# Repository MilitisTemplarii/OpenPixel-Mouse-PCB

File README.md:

# OpenPixel
# Mouse-PCB-STM32-PAW3395
BOM file soon :D

This is a mouse pcb based on stm32f215, usb3300 and paw3395

NO CODE, FIRMWARE, SOFTWARE, ETC, just a pcb design for hobby.

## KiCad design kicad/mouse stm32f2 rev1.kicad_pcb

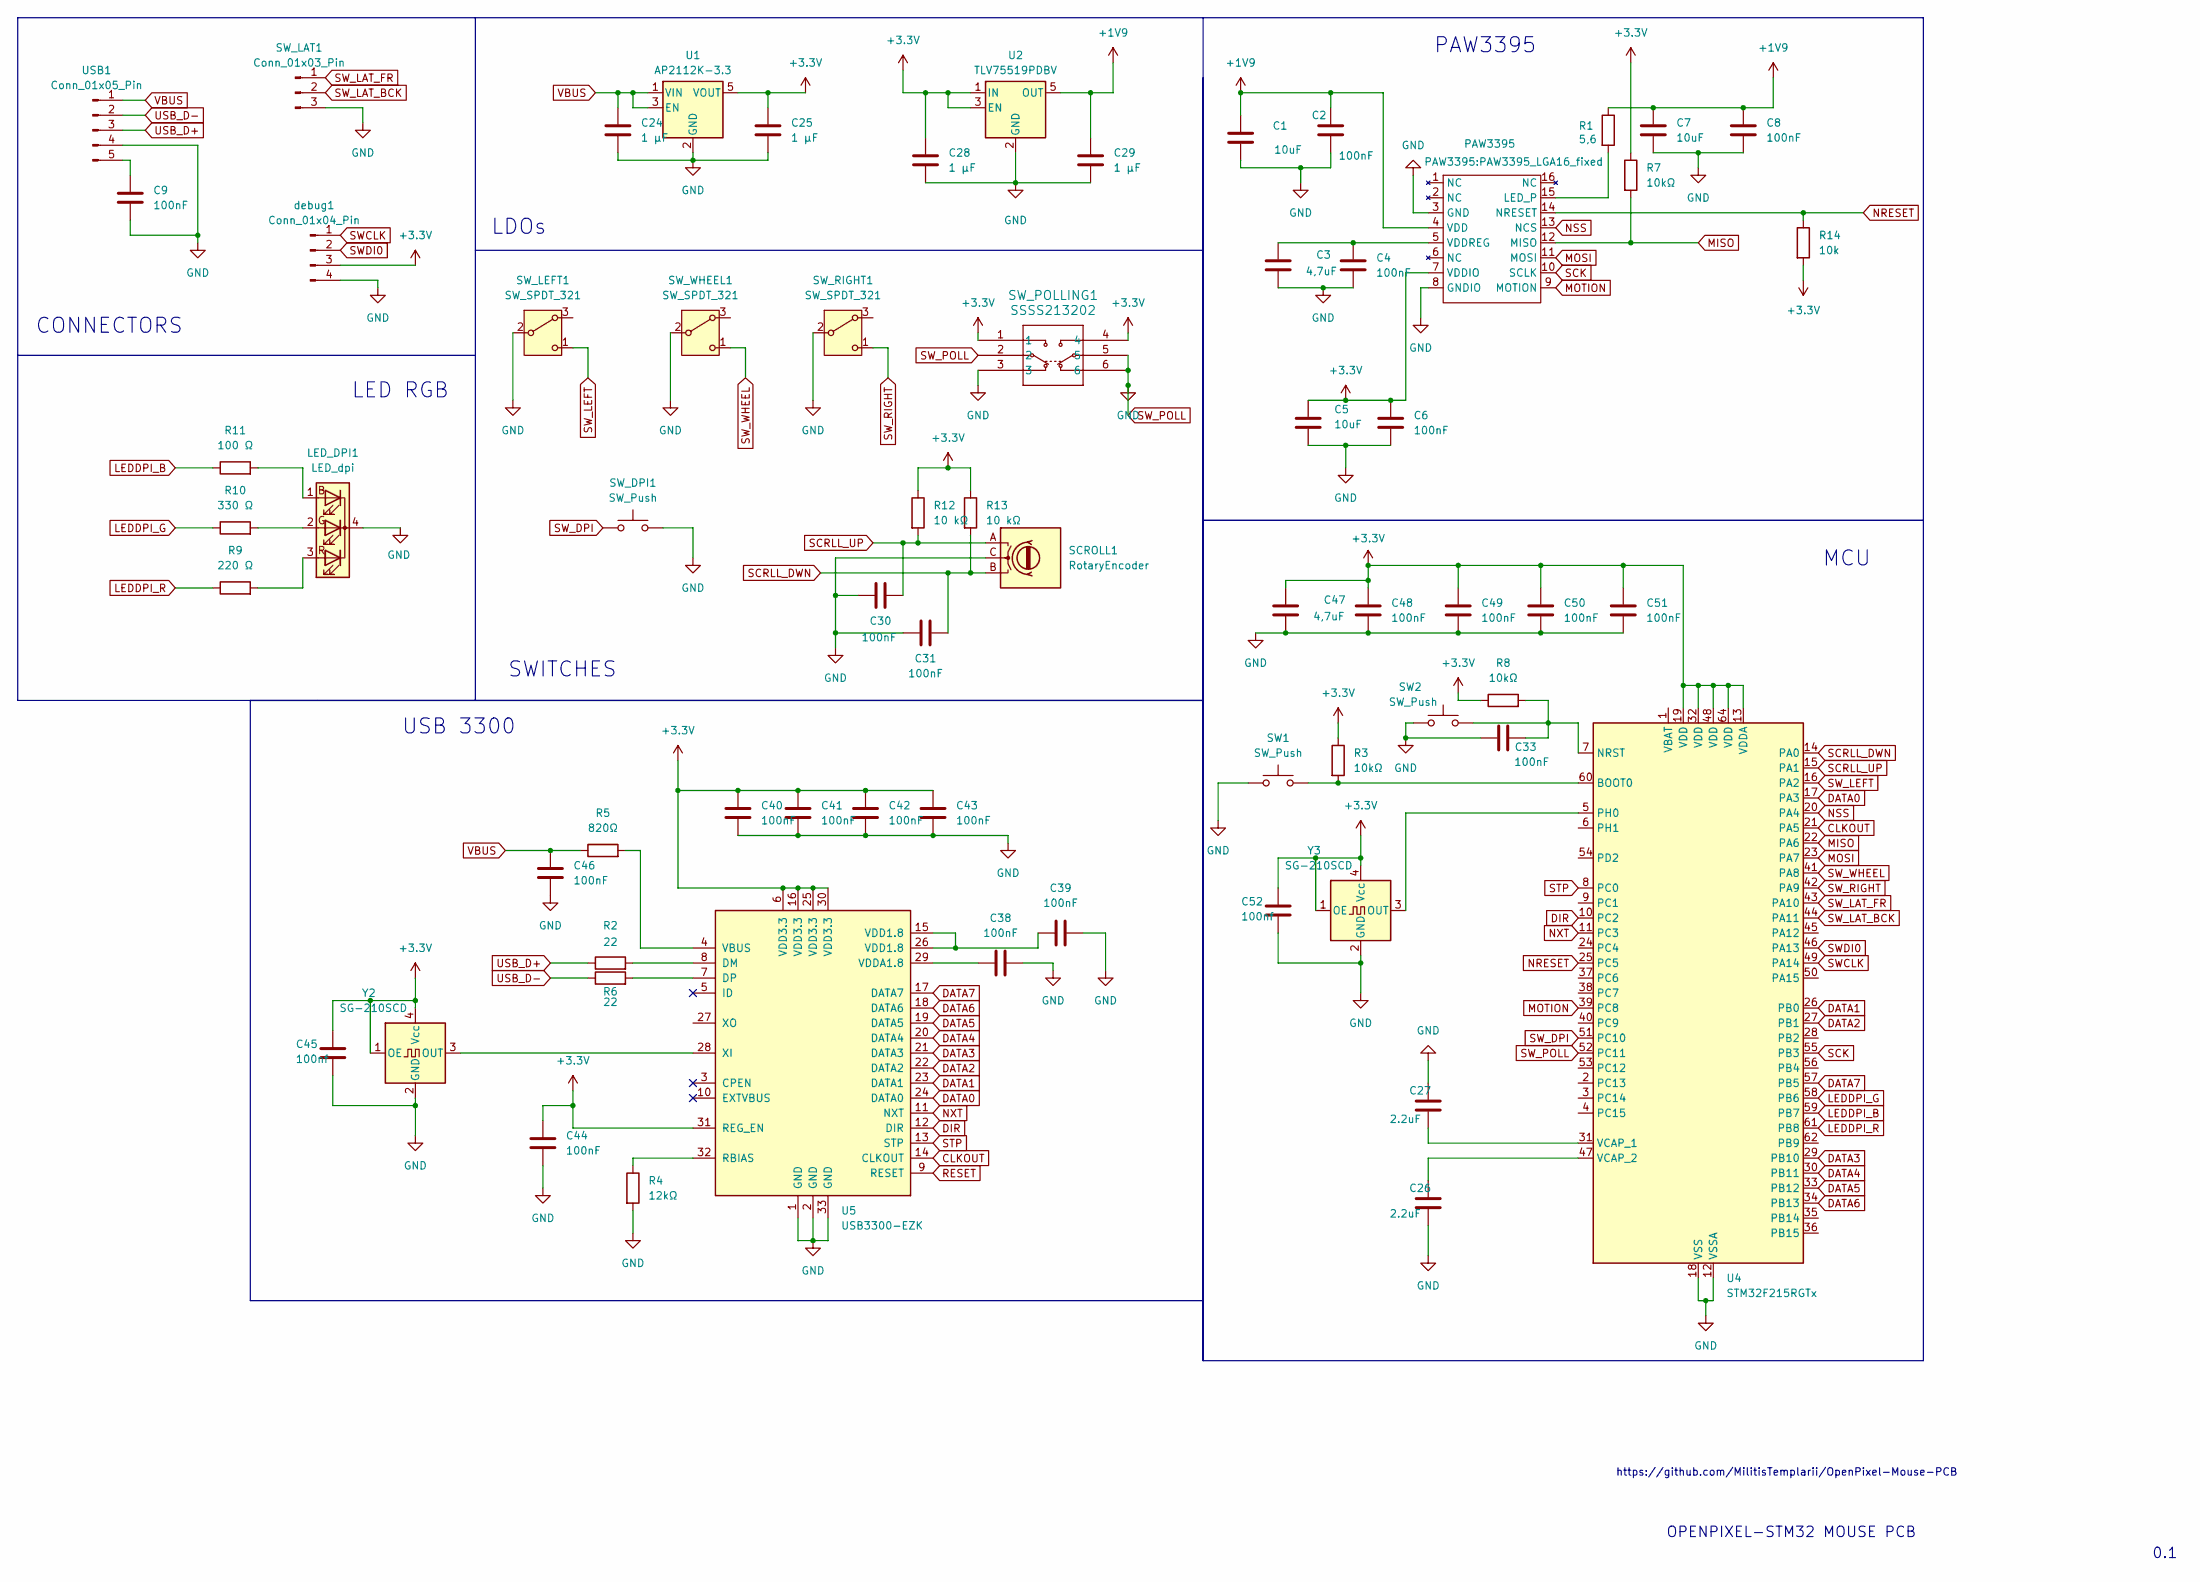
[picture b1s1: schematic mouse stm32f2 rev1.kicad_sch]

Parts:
C1, C5, C7: 10uF; C_0805_2012Metric
C2, C4, C6, C8, C9, C30, C31, C33, C38, C39, C40, C41, C42, C43, C44, C46, C48, C49, C50, C51: 100nF; C_0402_1005Metric
C3, C47: 4,7uF; C_0603_1608Metric
C24, C25, C28, C29: 1 µF; C_0402_1005Metric
C26, C27: 2.2uF; C_0402_1005Metric
C45, C52: 100nf; C_0402_1005Metric
LED_DPI1: LED_dpi; LED_RGB_1210
PAW3395: PAW3395_LGA16_fixed
R1: 5,6; R_0603_1608Metric
R2, R6: 22; R_0603_1608Metric
R3, R7, R8: 10kΩ; R_0603_1608Metric
R4: 12kΩ; R_0603_1608Metric
R5: 820Ω; R_0603_1608Metric
R9: 220 Ω; R_0603_1608Metric
R10: 330 Ω; R_0603_1608Metric
R11: 100 Ω; R_0603_1608Metric
R12, R13: 10 kΩ; R_0603_1608Metric
R14: 10k; R_0603_1608Metric
SCROLL1: RotaryEncoder; Encoder_Kailh_Wheel_3Pin
SW1: SW_Push; SW_SPST_TL3342
SW2: SW_Push; SW_SPST_EVQP7C
SW_DPI1: SW_Push; SW_SPST_TL3342
SW_LAT1: Conn_01x03_Pin; JST_SH_BM03B-SRSS-TB_1x03-1MP_P1.00mm_Vertical
SW_LEFT1: SW_SPDT_321; SW_D2FC_OMR
SW_POLLING1: SSSS213202; SSSS213202_AAL
SW_RIGHT1: SW_SPDT_321; SW_D2FC_OMR
SW_WHEEL1: SW_SPDT_321; SW_D2FC_OMR
U1: AP2112K-3.3; SOT-23-5
U2: TLV75519PDBV; SOT-23-5
U4: STM32F215RGTx; LQFP-64_10x10mm_P0.5mm
U5: USB3300-EZK; QFN-32-1EP_5x5mm_P0.5mm_EP3.45x3.45mm
USB1: Conn_01x05_Pin; JST_PH_S5B-PH-K_1x05_P2.00mm_Horizontal
Y2, Y3: SG-210SCD; Oscillator_SMD_SeikoEpson_SG210-4Pin_2.5x2.0mm
debug1: Conn_01x04_Pin; JST_PH_S4B-PH-K_1x04_P2.00mm_Horizontal

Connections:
+1V9: C1.1, C2.1, C7.1, C8.1, C29.1, PAW3395.4 (VDD), R1.1, U2.5 (OUT)
+3.3V: C5.1, C6.1, C25.1, C28.1, C40.1, C41.1, C42.1, C43.1, C44.1, C45.2, C47.1, C48.1, C49.1, C50.1, C51.1, C52.2, PAW3395.7 (VDDIO), R3.1, R7.1, R8.1, R12.1, R13.1, R14.2, SW_POLLING1.1, SW_POLLING1.4, U1.5 (VOUT), U2.1 (IN), U2.3 (EN), U4.13 (VDDA), U4.19 (VDD), U4.32 (VDD), U4.48 (VDD), U4.64 (VDD), U5.6 (VDD3.3), U5.16 (VDD3.3), U5.25 (VDD3.3), U5.30 (VDD3.3), U5.31 (REG_EN), Y2.1 (OE), Y2.4 (Vcc), Y3.1 (OE), Y3.4 (Vcc), debug1.3
CLKOUT: U4.21 (PA5), U5.14 (CLKOUT)
DATA0: U4.17 (PA3), U5.24 (DATA0)
DATA1: U4.26 (PB0), U5.23 (DATA1)
DATA2: U4.27 (PB1), U5.22 (DATA2)
DATA3: U4.29 (PB10), U5.21 (DATA3)
DATA4: U4.30 (PB11), U5.20 (DATA4)
DATA5: U4.33 (PB12), U5.19 (DATA5)
DATA6: U4.34 (PB13), U5.18 (DATA6)
DATA7: U4.57 (PB5), U5.17 (DATA7)
DIR: U4.10 (PC2), U5.12 (DIR)
LEDDPI_B: R11.1, U4.59 (PB7)
LEDDPI_G: R10.1, U4.58 (PB6)
LEDDPI_R: R9.1, U4.61 (PB8)
MISO: PAW3395.12 (MISO), R7.2, U4.22 (PA6)
MOSI: PAW3395.11 (MOSI), U4.23 (PA7)
MOTION: PAW3395.9 (MOTION), U4.39 (PC8)
NRESET: PAW3395.14 (NRESET), R14.1, U4.25 (PC5)
NSS: PAW3395.13 (NCS), U4.20 (PA4)
NXT: U4.11 (PC3), U5.11 (NXT)
unnamed: C39.1, U5.15 (VDD1.8), U5.26 (VDD1.8)
unnamed: LED_DPI1.1 (BA), R11.2
unnamed: LED_DPI1.2 (GA), R10.2
unnamed: LED_DPI1.3 (RA), R9.2
unnamed: PAW3395.15 (LED_P), R1.2
unnamed: C3.1, C4.1, PAW3395.5 (VDDREG)
unnamed: R3.2, SW1.2, U4.60 (BOOT0)
unnamed: C33.2, R8.2, SW2.2, U4.7 (NRST)
unnamed: U4.5 (PH0), Y3.3 (OUT)
unnamed: C27.2, U4.31 (VCAP_1)
unnamed: C26.1, U4.47 (VCAP_2)
unnamed: R2.2, U5.8 (DM)
unnamed: R6.2, U5.7 (DP)
unnamed: R4.1, U5.32 (RBIAS)
unnamed: R5.2, U5.4 (VBUS)
unnamed: C38.1, U5.29 (VDDA1.8)
unnamed: U5.28 (XI), Y2.3 (OUT)
unnamed: C9.1, USB1.5
RESET: U5.9 (RESET)
SCK: PAW3395.10 (SCLK), U4.55 (PB3)
SCRLL_DWN: C31.2, R13.2, SCROLL1.B, U4.14 (PA0)
SCRLL_UP: C30.2, R12.2, SCROLL1.A, U4.15 (PA1)
STP: U4.8 (PC0), U5.13 (STP)
SWCLK: U4.49 (PA14), debug1.1
SWDI0: U4.46 (PA13), debug1.2
SW_DPI: SW_DPI1.1, U4.51 (PC10)
SW_LAT_BCK: SW_LAT1.2, U4.44 (PA11)
SW_LAT_FR: SW_LAT1.1, U4.43 (PA10)
SW_LEFT: SW_LEFT1.1 (C), U4.16 (PA2)
SW_RIGHT: SW_RIGHT1.1 (C), U4.42 (PA9)
SW_WHEEL: SW_WHEEL1.1 (C), U4.41 (PA8)
USB_D+: R2.1, USB1.3
USB_D-: R6.1, USB1.2
VBUS: C24.1, C46.2, R5.1, U1.1 (VIN), U1.3 (EN), USB1.1

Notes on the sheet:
USB 3300
PAW3395
0.1
MCU
https://github.com/MilitisTemplarii/OpenPixel-Mouse-PCB
SWITCHES
LDOs
CONNECTORS
OPENPIXEL-STM32 MOUSE PCB
LED RGB

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
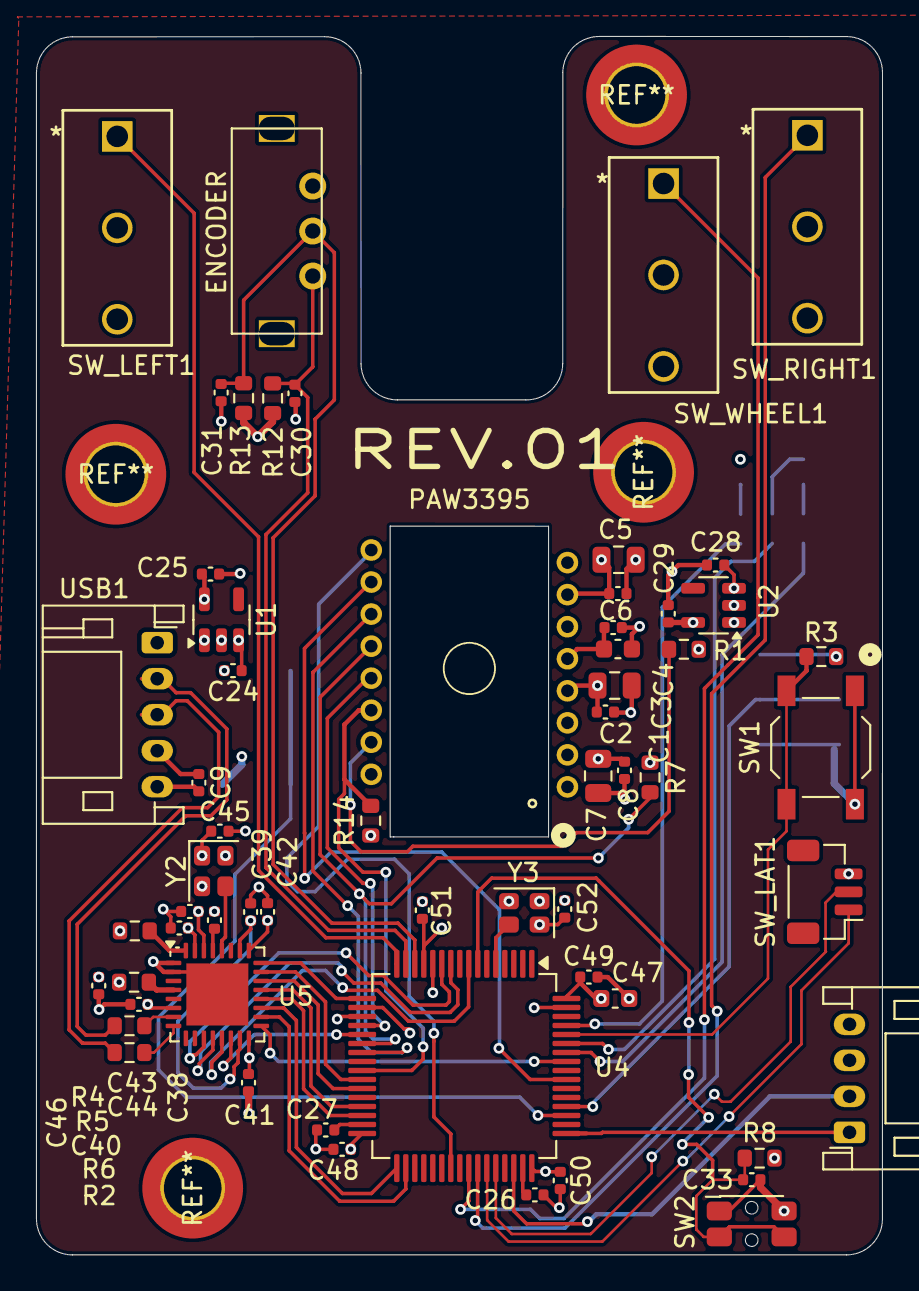
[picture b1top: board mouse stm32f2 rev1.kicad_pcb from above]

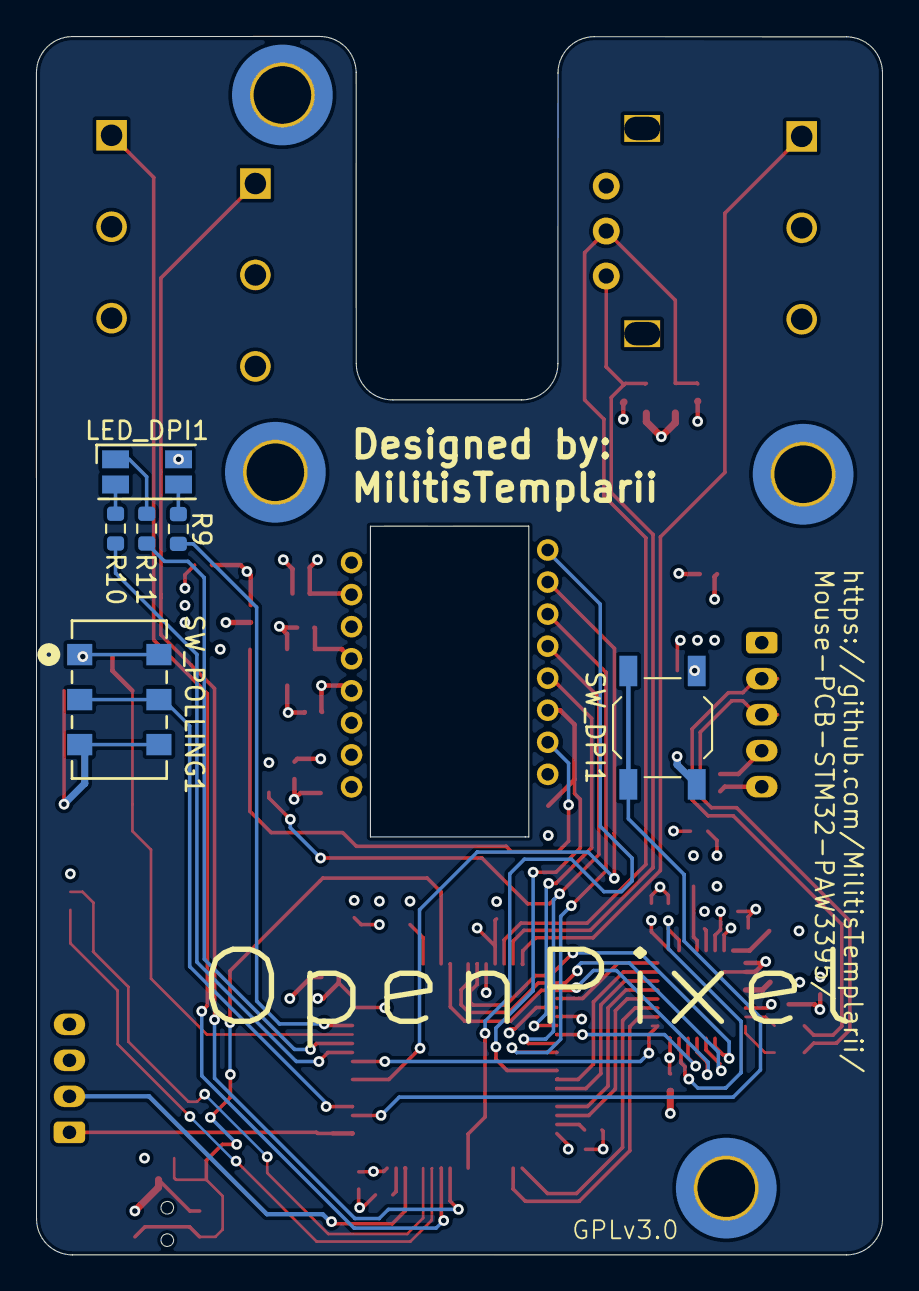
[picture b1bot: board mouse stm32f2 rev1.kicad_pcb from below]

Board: 4 copper layers, 47.0 x 67.7 mm, 66 parts (6 on the bottom side), 56 nets.

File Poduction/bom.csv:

Designator,Footprint,Quantity,Value,LCSC Part #
"C1, C5, C7",805,3,10 uF,
"C2, C30, C31, C33, C38, C39, C4, C40, C41, C42, C43, C44, C45, C46, C48, C49, C50, C51, C52, C6, C8, C9",402,22,100 nF,
"C24, C25, C28, C29",402,4,1 µF,
"C26, C27",402,2,2.2 uF,
"C3, C47",603,2,"4,7 uF",
DEBUG1,JST_PH_S4B-PH-K_1x04_P2.00mm_Horizontal,1,Conn_01x04_Pin,
LED_DPI1,LED_RGB_1210,1,SB1210WC01-RGB ,
PAW3395,PAW3395_LGA16_fixed,1,~,
R1,603,1,"5,6 Ω",
R10,603,1,330 Ω,
R11,603,1,100 Ω,
"R12, R13",603,2,10 kΩ,
R14,603,1,10 kΩ,
"R2, R6",603,2,22 Ω,
"R3, R7, R8",603,3,10kΩ,
R4,603,1,12kΩ,
R5,603,1,820Ω,
R9,603,1,220 Ω,
SCROLL1,Encoder_Kailh_Wheel_3Pin,1,CEN981012R24,
"SW1, SW_DPI1",SW_SPST_TL3342,2,SW_Push,
SW2,SW_SPST_EVQP7C,1,SW_Push,
SW_LAT1,JST_SH_BM03B-SRSS-TB_1x03-1MP_P1.00mm_Vertical,1,Conn_01x03_Pin,
"SW_LEFT1, SW_RIGHT1, SW_WHEEL1",SW_D2FC_OMR,3,SW_SPDT_321,
SW_POLLING1,SSSS213202_AAL,1,SSSS213202,
U1,SOT-23-5,1,AP2112K-3.3,
U2,SOT-23-5,1,TLV75519PDBV,
U4,LQFP-64_10x10mm_P0.5mm,1,STM32F215RGTx,
U5,QFN-32-1EP_5x5mm_P0.5mm_EP3.45x3.45mm,1,USB3300-EZK,
USB1,JST_PH_S5B-PH-K_1x05_P2.00mm_Horizontal,1,Conn_01x05_Pin,
Y2,Oscillator_SMD_24MHz_2.5x2.0mm,1,OT252024MJBA4SL,
Y3,Oscillator_SMD_8MHz_2.5x2.0mm,1,OT3EL89CJI-111YLC-8M,

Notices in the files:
kicad/mouse stm32f2 rev1.kicad_pcb:
GPLv3.0
